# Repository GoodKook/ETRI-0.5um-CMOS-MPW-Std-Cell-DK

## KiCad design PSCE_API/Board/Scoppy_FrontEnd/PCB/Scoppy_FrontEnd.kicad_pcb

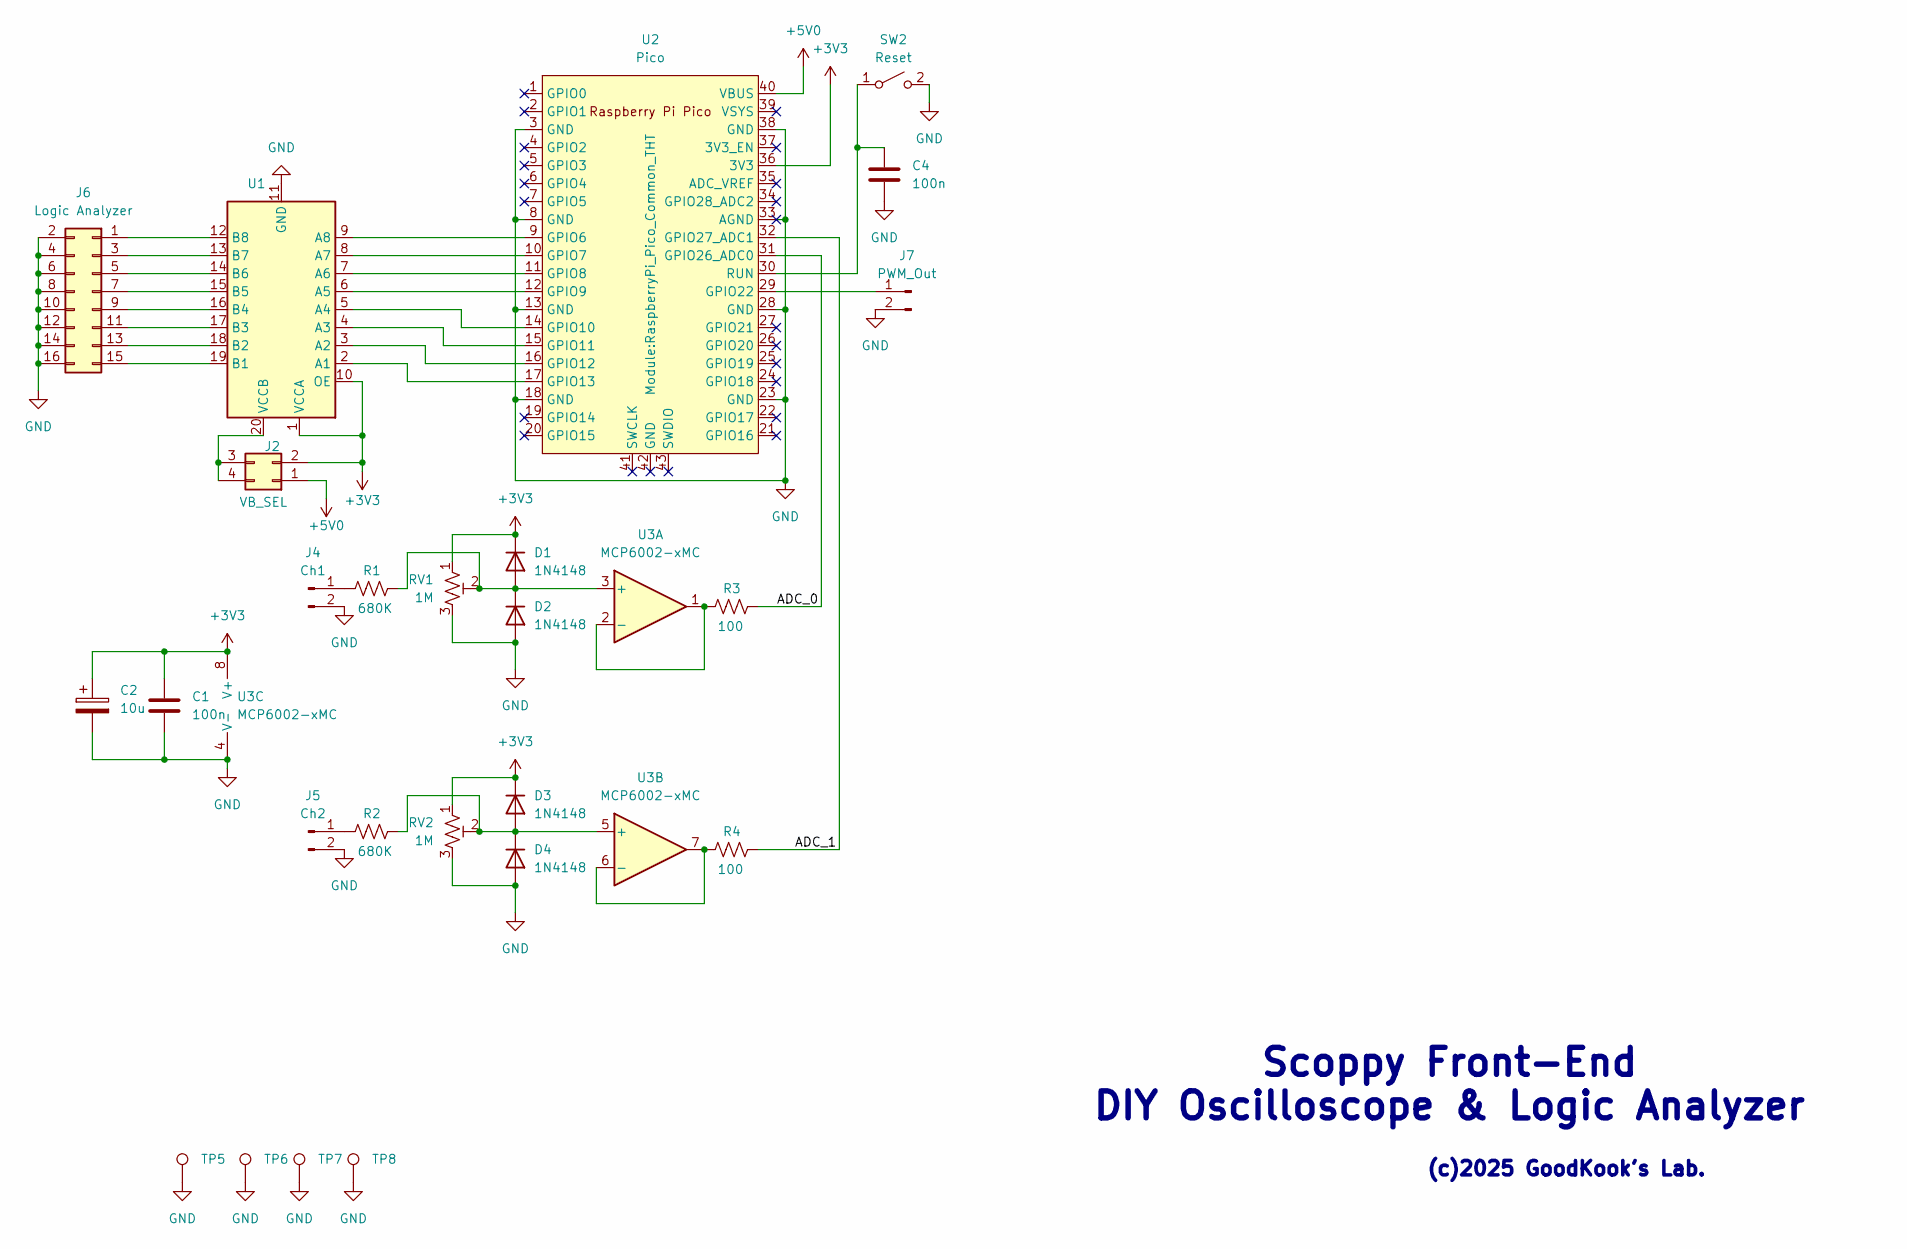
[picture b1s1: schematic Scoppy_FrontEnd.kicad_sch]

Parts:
C1, C4: 100n; C_Disc_D3.8mm_W2.6mm_P2.50mm
C2: 10u; CP_Radial_Tantal_D9.0mm_P2.50mm
D1, D2, D3, D4: 1N4148; D_DO-35_SOD27_P7.62mm_Horizontal
J2: VB_SEL; PinHeader_2x02_P2.54mm_Vertical
J4: Ch1; PinHeader_2x01_P2.54mm_Vertical
J5: Ch2; PinHeader_2x01_P2.54mm_Vertical
J6: Logic Analyzer; PinHeader_2x08_P2.54mm_Vertical
J7: PWM_Out; PinHeader_2x01_P2.54mm_Vertical
R1, R2: 680K; R_Axial_DIN0204_L3.6mm_D1.6mm_P7.62mm_Horizontal
R3, R4: 100; R_Axial_DIN0204_L3.6mm_D1.6mm_P7.62mm_Horizontal
RV1, RV2: 1M; Potentiometer_Runtron_RM-065_Vertical
SW2: Reset; SW_PUSH_6mm_H5mm
TP5, TP6, TP7, TP8: Mounting Hole; MountingHole_3.2mm_M3
U1: Level_Shifter_Module_HW-221
U2: Pico; RaspberryPi_Pico_Common_THT
U3: MCP6002-xMC; DIP-8_W10.16mm_LongPads

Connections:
+3V3: C1.1, C2.1, D1.1 (K), D3.1 (K), J2.2, RV1.1, RV2.1, U1.1 (VCCA), U1.10 (OE), U2.36 (3V3), U3.8 (V+)
+5V0: J2.1, U2.40 (VBUS)
/ADC_0: R3.1, U2.31 (GPIO26_ADC0)
/ADC_1: R4.1, U2.32 (GPIO27_ADC1)
GND: C1.2, C2.2, C4.2, D2.2 (A), D4.2 (A), J4.2, J5.2, J6.2, J6.4, J6.6, J6.8, J6.10, J6.12, J6.14, J6.16, J7.2, RV1.3, RV2.3, SW2.2 (B), TP5.1, TP6.1, TP7.1, TP8.1, U1.11 (GND), U2.3 (GND), U2.8 (GND), U2.13 (GND), U2.18 (GND), U2.23 (GND), U2.28 (GND), U2.33 (AGND), U2.38 (GND), U3.4 (V-), U3.9 (V-)
unnamed: D1.2 (A), D2.1 (K), R1.1, RV1.2, U3.3 (+)
unnamed: D3.2 (A), D4.1 (K), R2.1, RV2.2, U3.5 (+)
unnamed: J2.3, J2.4, U1.20 (VCCB)
unnamed: J4.1, R1.2
unnamed: J5.1, R2.2
unnamed: J6.1, U1.12 (B8)
unnamed: J6.3, U1.13 (B7)
unnamed: J6.5, U1.14 (B6)
unnamed: J6.7, U1.15 (B5)
unnamed: J6.9, U1.16 (B4)
unnamed: J6.11, U1.17 (B3)
unnamed: J6.13, U1.18 (B2)
unnamed: J6.15, U1.19 (B1)
unnamed: J7.1, U2.29 (GPIO22)
unnamed: C4.1, SW2.1 (A), U2.30 (RUN)
unnamed: U1.2 (A1), U2.17 (GPIO13)
unnamed: U1.3 (A2), U2.16 (GPIO12)
unnamed: U1.4 (A3), U2.15 (GPIO11)
unnamed: U1.5 (A4), U2.14 (GPIO10)
unnamed: U1.6 (A5), U2.12 (GPIO9)
unnamed: U1.7 (A6), U2.11 (GPIO8)
unnamed: U1.8 (A7), U2.10 (GPIO7)
unnamed: U1.9 (A8), U2.9 (GPIO6)
unnamed: R3.2, U3.1, U3.2 (-)
unnamed: R4.2, U3.6 (-), U3.7

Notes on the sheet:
Scoppy Front-End DIY Oscilloscope & Logic Analyzer
(c)2025 GoodKook's Lab.

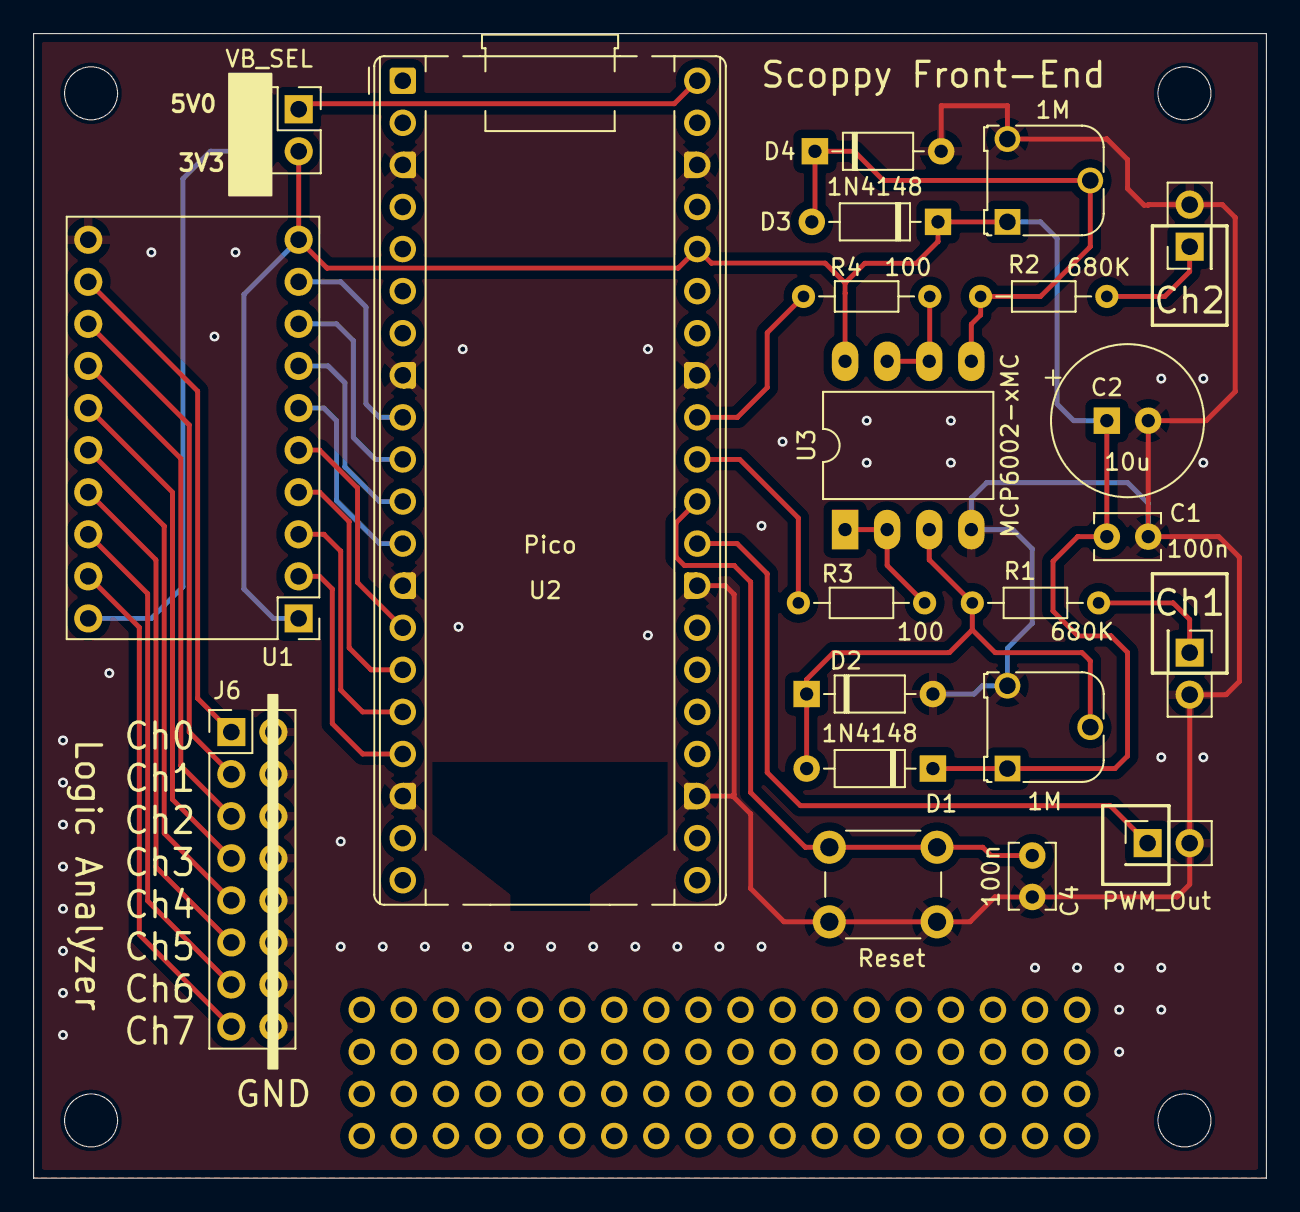
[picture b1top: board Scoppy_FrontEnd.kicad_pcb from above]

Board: 2 copper layers, 74.4 x 69.1 mm, 26 parts (0 on the bottom side), 30 nets.

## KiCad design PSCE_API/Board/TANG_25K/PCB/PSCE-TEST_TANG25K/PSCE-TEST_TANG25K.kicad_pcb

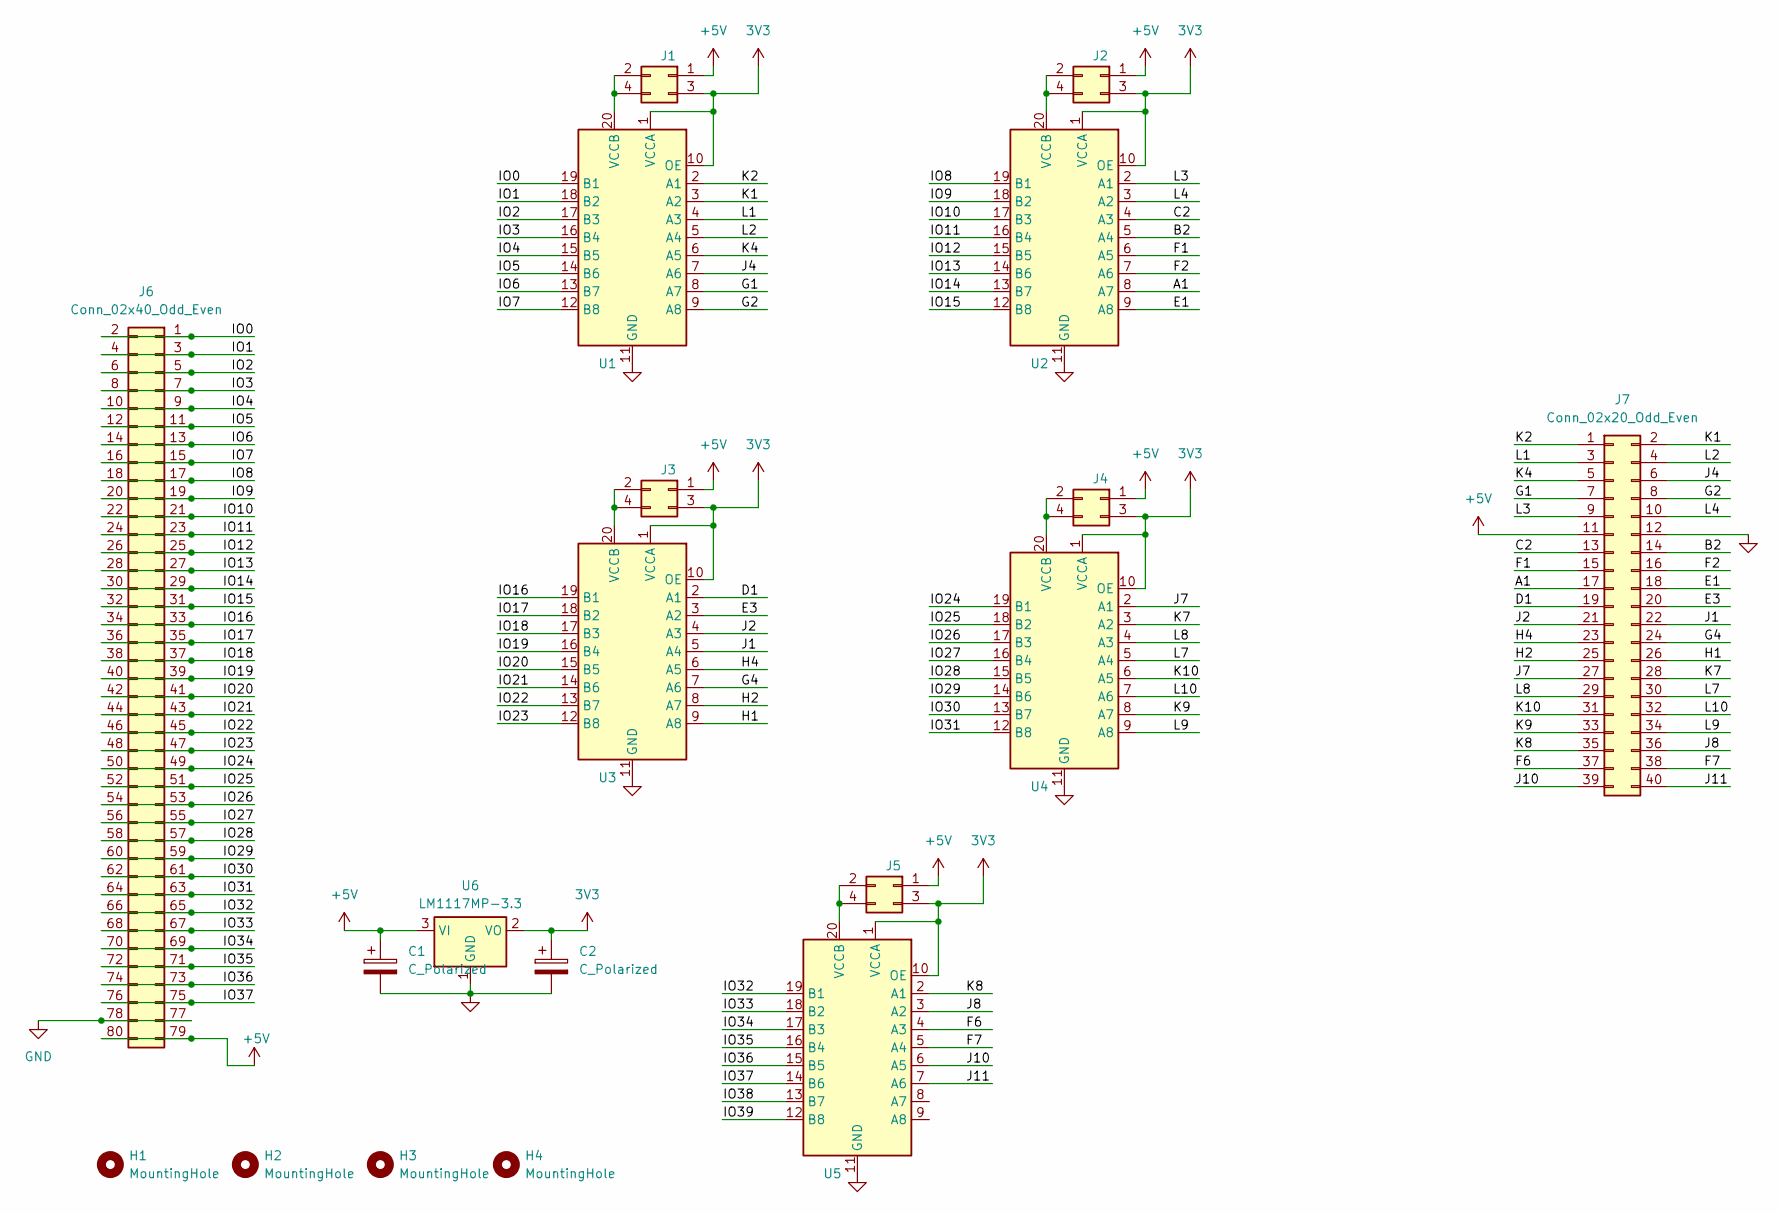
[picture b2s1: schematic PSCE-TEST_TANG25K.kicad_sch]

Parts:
C1, C2: C_Polarized; C_1206_3216Metric_Pad1.33x1.80mm_HandSolder
H1, H2, H3, H4: MountingHole; MountingHole_3.5mm
J1, J2, J3, J4, J5: Conn_02x02_Odd_Even; PinHeader_2x02_P2.54mm_Vertical
J6: Conn_02x40_Odd_Even; PinHeader_2x40_P2.54mm_Vertical
J7: Conn_02x20_Odd_Even; PinHeader_2x20_P2.54mm_Vertical
U1, U2, U3, U4, U5: Level_Shifter_Module_HW-221
U6: LM1117MP-3.3; SOT-223-3_TabPin2

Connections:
3V3: C2.1, J1.3, J2.3, J3.3, J4.3, J5.3, U1.1 (VCCA), U1.10 (OE), U2.1 (VCCA), U2.10 (OE), U3.1 (VCCA), U3.10 (OE), U4.1 (VCCA), U4.10 (OE), U5.1 (VCCA), U5.10 (OE), U6.2 (VO)
+5V: C1.1, J1.1, J2.1, J3.1, J4.1, J5.1, J6.79, J6.80, J7.11, U6.3 (VI)
/A1: J7.17, U2.8 (A7)
/B2: J7.14, U2.5 (A4)
/C2: J7.13, U2.4 (A3)
/D1: J7.19, U3.2 (A1)
/E1: J7.18, U2.9 (A8)
/E3: J7.20, U3.3 (A2)
/F1: J7.15, U2.6 (A5)
/F2: J7.16, U2.7 (A6)
/F6: J7.37, U5.4 (A3)
/F7: J7.38, U5.5 (A4)
/G1: J7.7, U1.8 (A7)
/G2: J7.8, U1.9 (A8)
/G4: J7.24, U3.7 (A6)
/H1: J7.26, U3.9 (A8)
/H2: J7.25, U3.8 (A7)
/H4: J7.23, U3.6 (A5)
/IO0: J6.1, J6.2, U1.19 (B1)
/IO1: J6.3, J6.4, U1.18 (B2)
/IO2: J6.5, J6.6, U1.17 (B3)
/IO3: J6.7, J6.8, U1.16 (B4)
/IO4: J6.9, J6.10, U1.15 (B5)
/IO5: J6.11, J6.12, U1.14 (B6)
/IO6: J6.13, J6.14, U1.13 (B7)
/IO7: J6.15, J6.16, U1.12 (B8)
/IO8: J6.17, J6.18, U2.19 (B1)
/IO9: J6.19, J6.20, U2.18 (B2)
/IO10: J6.21, J6.22, U2.17 (B3)
/IO11: J6.23, J6.24, U2.16 (B4)
/IO12: J6.25, J6.26, U2.15 (B5)
/IO13: J6.27, J6.28, U2.14 (B6)
/IO14: J6.29, J6.30, U2.13 (B7)
/IO15: J6.31, J6.32, U2.12 (B8)
/IO16: J6.33, J6.34, U3.19 (B1)
/IO17: J6.35, J6.36, U3.18 (B2)
/IO18: J6.37, J6.38, U3.17 (B3)
/IO19: J6.39, J6.40, U3.16 (B4)
/IO20: J6.41, J6.42, U3.15 (B5)
/IO21: J6.43, J6.44, U3.14 (B6)
/IO22: J6.45, J6.46, U3.13 (B7)
/IO23: J6.47, J6.48, U3.12 (B8)
/IO24: J6.49, J6.50, U4.19 (B1)
/IO25: J6.51, J6.52, U4.18 (B2)
/IO26: J6.53, J6.54, U4.17 (B3)
/IO27: J6.55, J6.56, U4.16 (B4)
/IO28: J6.57, J6.58, U4.15 (B5)
/IO29: J6.59, J6.60, U4.14 (B6)
/IO30: J6.61, J6.62, U4.13 (B7)
/IO31: J6.63, J6.64, U4.12 (B8)
/IO32: J6.65, J6.66, U5.19 (B1)
/IO33: J6.67, J6.68, U5.18 (B2)
/IO34: J6.69, J6.70, U5.17 (B3)
/IO35: J6.71, J6.72, U5.16 (B4)
/IO36: J6.73, J6.74, U5.15 (B5)
/IO37: J6.75, J6.76, U5.14 (B6)
/IO38: U5.13 (B7)
/IO39: U5.12 (B8)
/J1: J7.22, U3.5 (A4)
/J2: J7.21, U3.4 (A3)
/J4: J7.6, U1.7 (A6)
/J7: J7.27, U4.2 (A1)
/J8: J7.36, U5.3 (A2)
/J10: J7.39, U5.6 (A5)
/J11: J7.40, U5.7 (A6)
/K1: J7.2, U1.3 (A2)
/K2: J7.1, U1.2 (A1)
/K4: J7.5, U1.6 (A5)
/K7: J7.28, U4.3 (A2)
/K8: J7.35, U5.2 (A1)
/K9: J7.33, U4.8 (A7)
/K10: J7.31, U4.6 (A5)
/L1: J7.3, U1.4 (A3)
/L2: J7.4, U1.5 (A4)
/L3: J7.9, U2.2 (A1)
/L4: J7.10, U2.3 (A2)
/L7: J7.30, U4.5 (A4)
/L8: J7.29, U4.4 (A3)
/L9: J7.34, U4.9 (A8)
/L10: J7.32, U4.7 (A6)
GND: C1.2, C2.2, J6.77, J6.78, J7.12, U1.11 (GND), U2.11 (GND), U3.11 (GND), U4.11 (GND), U5.11 (GND), U6.1 (GND)
unnamed: J1.2, J1.4, U1.20 (VCCB)
unnamed: J2.2, J2.4, U2.20 (VCCB)
unnamed: J3.2, J3.4, U3.20 (VCCB)
unnamed: J4.2, J4.4, U4.20 (VCCB)
unnamed: J5.2, J5.4, U5.20 (VCCB)

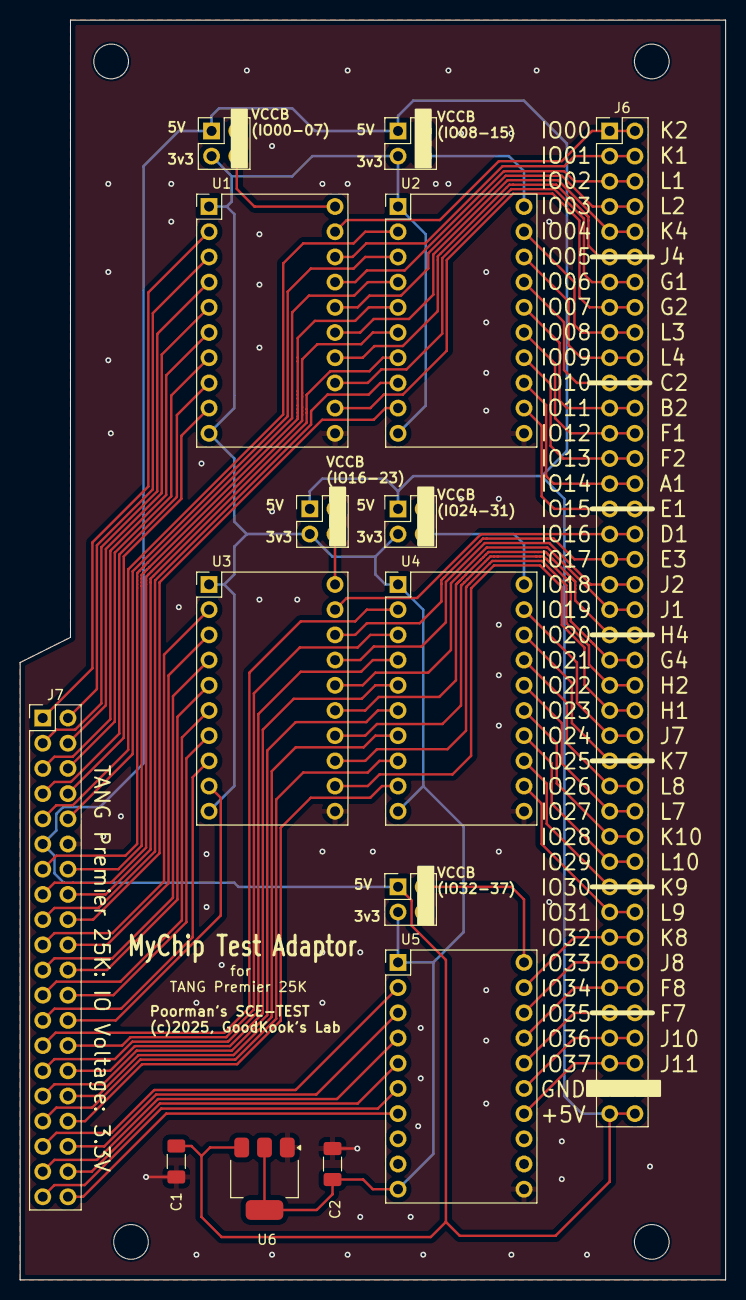
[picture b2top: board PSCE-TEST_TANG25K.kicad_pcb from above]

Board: 2 copper layers, 71.1 x 127.0 mm, 19 parts (0 on the bottom side), 84 nets.

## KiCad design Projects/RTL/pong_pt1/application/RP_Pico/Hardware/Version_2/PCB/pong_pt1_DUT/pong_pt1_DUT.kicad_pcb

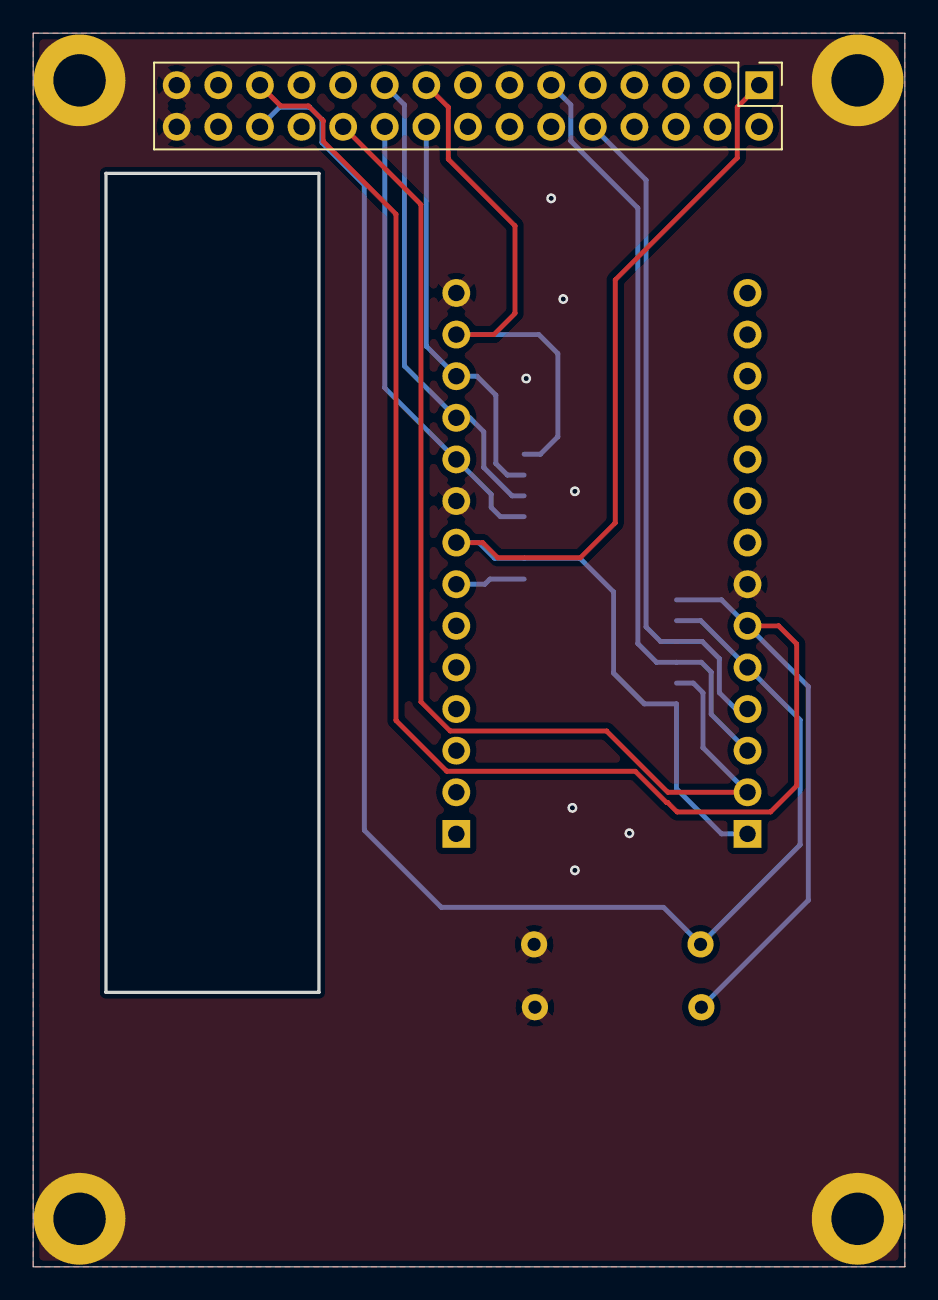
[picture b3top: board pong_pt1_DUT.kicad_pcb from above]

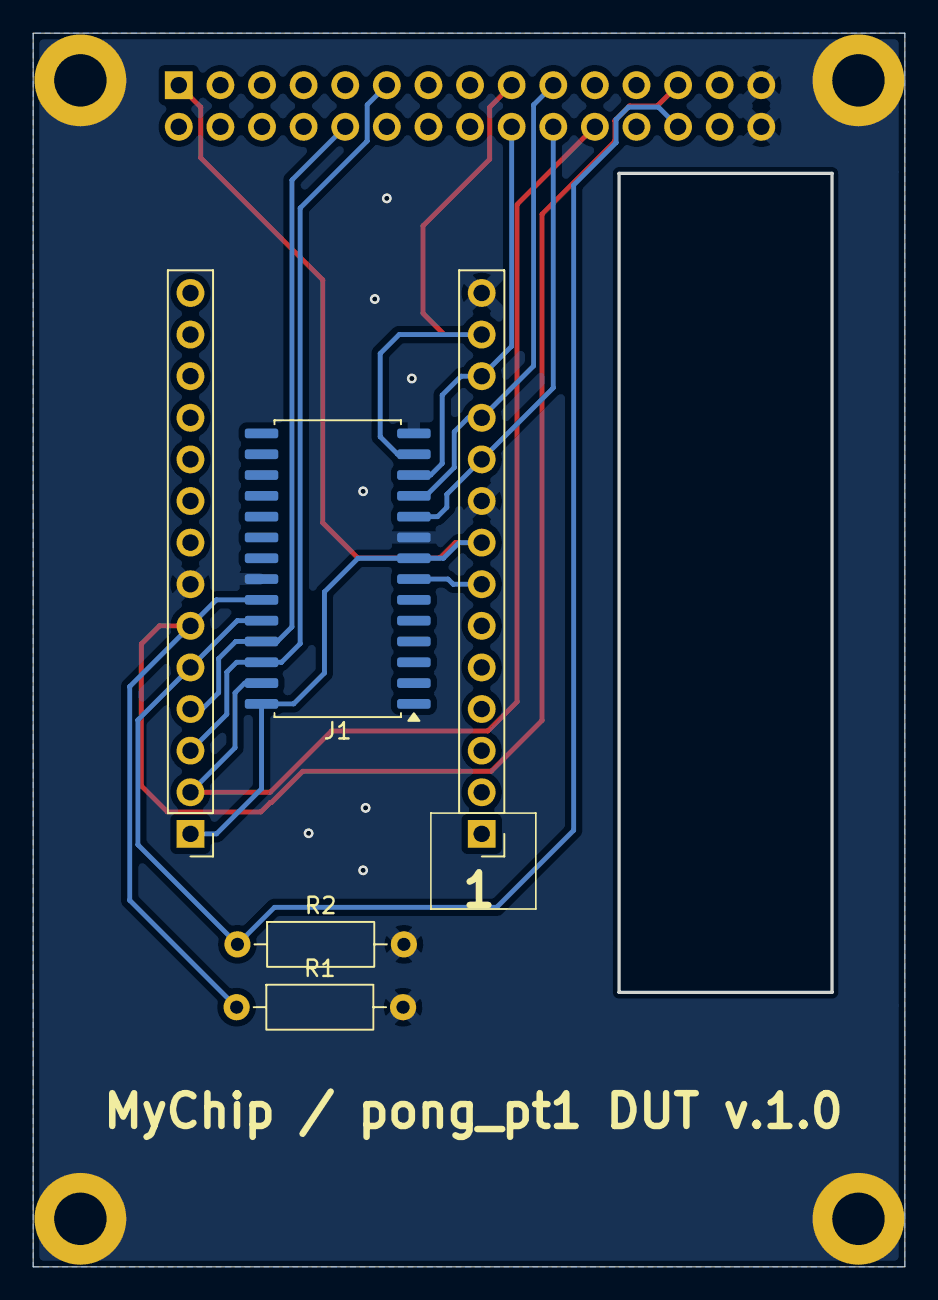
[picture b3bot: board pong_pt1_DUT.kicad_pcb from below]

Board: 2 copper layers, 53.2 x 75.3 mm, 10 parts (5 on the bottom side), 12 nets.

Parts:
H1, H2, H5, H6: MountingHole_Pad; MountingHole_3.2mm_M3_DIN965_Pad
J1: MyChip; SOIC-28W_7.5x17.9mm_P1.27mm
J2: MyChip_L; PinHeader_1x14_P2.54mm_Vertical
J3: MyChip_R; PinHeader_1x14_P2.54mm_Vertical
J4: Conn_02x15_Odd_Even; PinHeader_2x15_P2.54mm_Vertical
R1, R2: 47K; R_Axial_DIN0207_L6.3mm_D2.5mm_P10.16mm_Horizontal

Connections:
+3V3: J1.8, J1.28, J2.8, J3.1, J4.1
/clk: J1.27, J3.2, J4.22
/down: J1.24, J3.5, J4.26, R2.1
/enable: J1.26, J3.3, J4.11
/hsync: J1.12, J2.12, J4.18
/p_tick: J1.13, J2.13, J4.17
/reset: J1.25, J3.4, J4.10
/rgb: J1.10, J2.10, J4.20
/up: J1.23, J3.6, J4.25, R1.1
/vsync: J1.11, J2.11, J4.19
GND: H1.1 (1_1), H2.1 (1_1), H5.1 (1_1), H6.1 (1_1), J1.9, J1.14, J1.22, J2.9, J2.14, J3.7, J4.29, J4.30, R1.2, R2.2
unnamed: J1.7, J2.7

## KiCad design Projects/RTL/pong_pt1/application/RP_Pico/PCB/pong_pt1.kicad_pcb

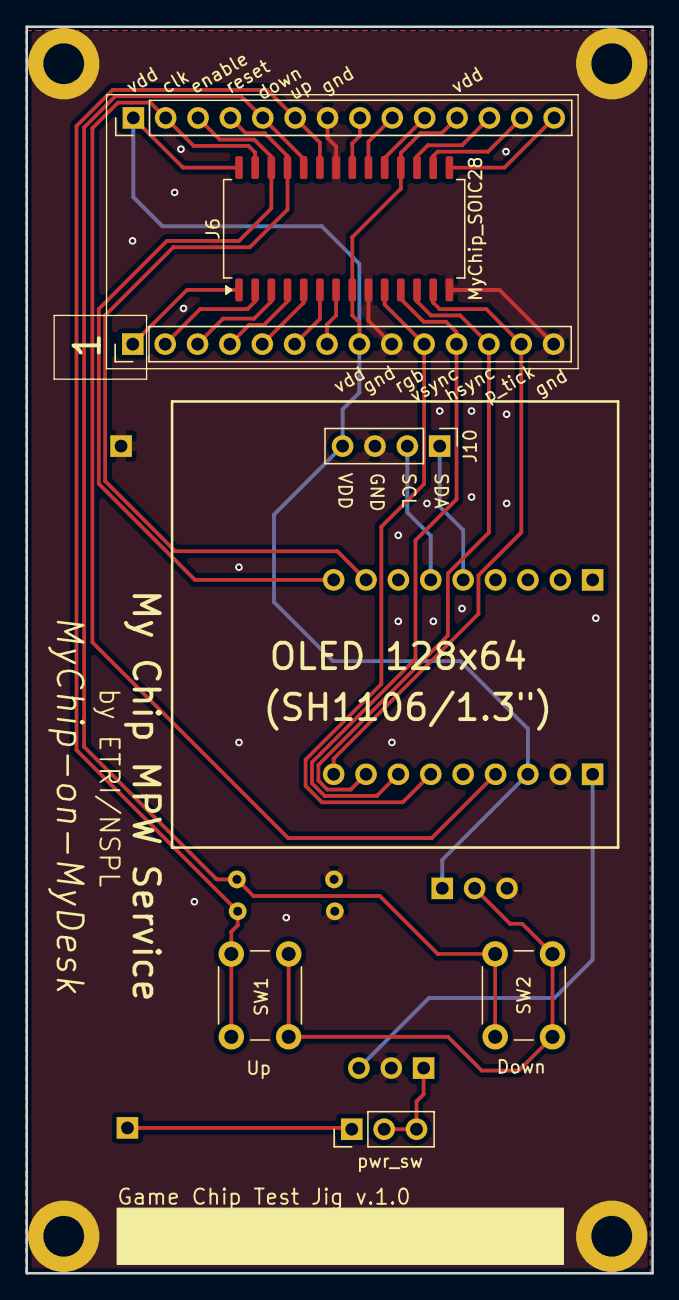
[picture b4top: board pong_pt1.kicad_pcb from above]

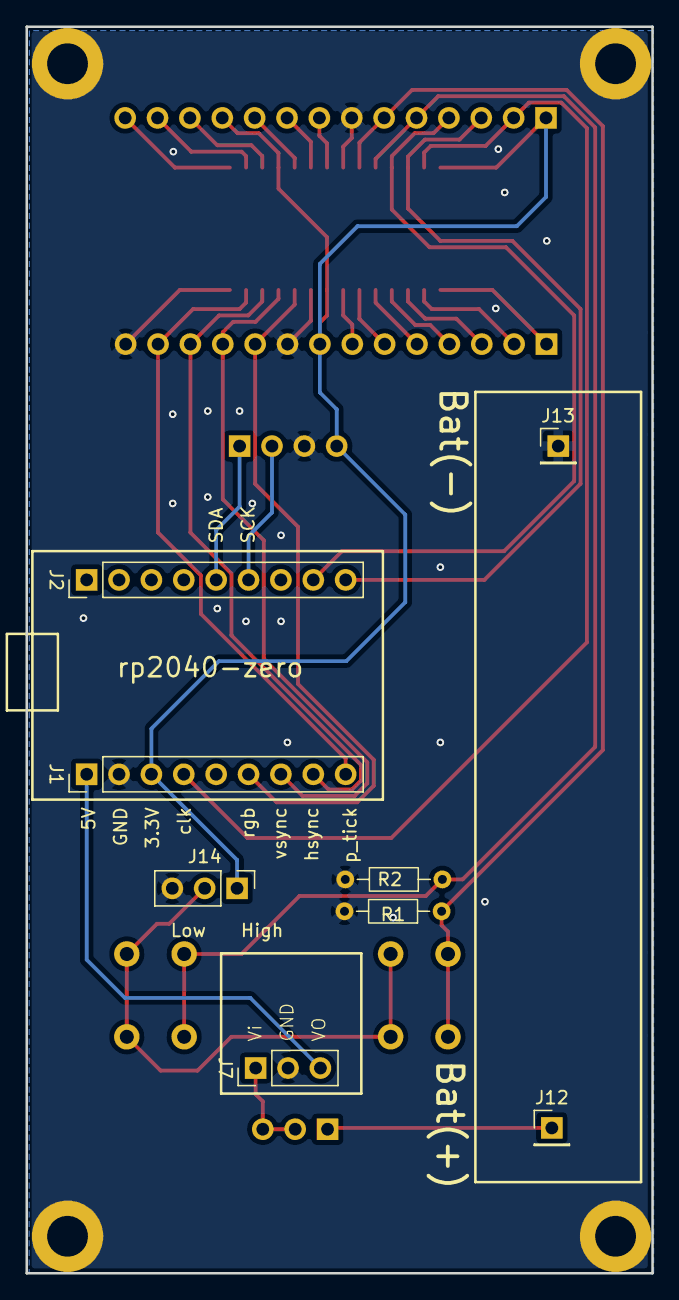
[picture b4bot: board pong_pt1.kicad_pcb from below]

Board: 2 copper layers, 49.1 x 97.8 mm, 19 parts (8 on the bottom side), 24 nets.

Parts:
H1, H2, H5, H6: MountingHole_Pad; MountingHole_3.2mm_M3_DIN965_Pad
J1: RP_L; PinHeader_1x09_P2.54mm_Vertical
J2: RP_R; PinHeader_1x09_P2.54mm_Vertical
J4: L; PinHeader_1x14_P2.54mm_Vertical
J5: R; PinHeader_1x14_P2.54mm_Vertical
J6: MyChip_SOIC28; SOIC-28W_7.5x18.7mm_P1.27mm
J7: DC-DC; PinHeader_1x03_P2.54mm_Vertical
J10: OLED128x64; PinHeader_1x04_P2.54mm_Vertical
J11: pwr_sw; PinHeader_1x03_P2.54mm_Vertical
J12: Bat(+); PinHeader_1x01_P2.54mm_Vertical
J13: Bat(-); PinHeader_1x01_P2.54mm_Vertical
J14: PinHeader_1x03_P2.54mm_Vertical
R1, R2: 47K; R_Axial_DIN0204_L3.6mm_D1.6mm_P7.62mm_Horizontal
SW1: Up; SW_PUSH_6mm
SW2: Down; SW_PUSH_6mm

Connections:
+3V3: J1.3, J4.8, J5.1, J5.11, J6.8, J6.18, J6.28, J10.4, J14.1
+5V: J1.1, J7.3
/Bat+: J11.1, J12.1 (Pin_1_1)
/COMM: J14.2, SW1.2, SW2.2
/SCL: J2.6, J10.2
/SDA: J2.5, J10.1
/Vi: J7.1, J11.2, J11.3
/clk: J1.4, J5.2, J6.27
/down: J5.5, J6.24, R2.1, SW2.1
/enable: J2.9, J5.3, J6.26
/hsync: J1.8, J4.12, J6.12
/p_tick: J1.9, J4.13, J6.13
/reset: J2.8, J5.4, J6.25
/rgb: J1.6, J4.10, J6.10
/up: J5.6, J6.23, R1.1, SW1.1
/vsync: J1.7, J4.11, J6.11
GND: H1.1 (1_1), H2.1 (1_1), H5.1 (1_1), H6.1 (1_1), J1.2, J4.9, J4.14, J5.7, J6.9, J6.14, J6.22, J7.2, J10.3, J13.1 (Pin_1_1), J14.3, R1.2, R2.2
unnamed: J4.1, J6.1
unnamed: J4.2, J6.2
unnamed: J4.3, J6.3
unnamed: J4.4, J6.4
unnamed: J4.5, J6.5
unnamed: J4.6, J6.6
unnamed: J4.7, J6.7

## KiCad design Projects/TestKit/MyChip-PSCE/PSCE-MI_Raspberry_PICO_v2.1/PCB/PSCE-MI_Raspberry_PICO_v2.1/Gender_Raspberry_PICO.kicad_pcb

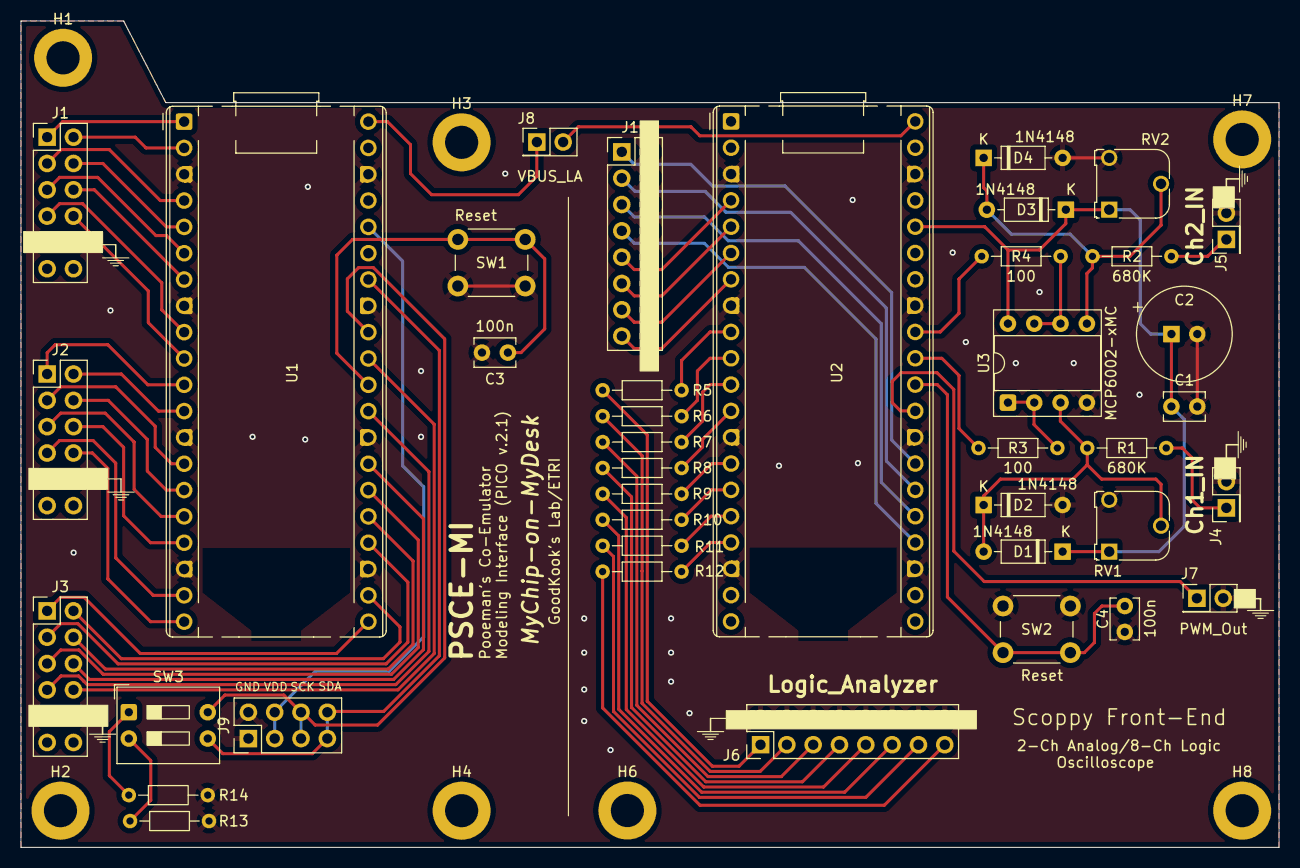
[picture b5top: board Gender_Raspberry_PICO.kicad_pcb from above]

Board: 2 copper layers, 121.4 x 79.8 mm, 47 parts (0 on the bottom side), 68 nets.

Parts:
C1, C3, C4: 100n; C_Disc_D3.8mm_W2.6mm_P2.50mm
C2: 10u; CP_Radial_Tantal_D9.0mm_P2.50mm
D1, D2, D3, D4: 1N4148; D_DO-35_SOD27_P7.62mm_Horizontal
H1, H2, H3, H4, H6, H7, H8: MountingHole; MountingHole_3.2mm_M3_DIN965_Pad
J1: FPGA_A; PinHeader_2x06_P2.54mm_Vertical
J2: FPGA_B; PinHeader_2x06_P2.54mm_Vertical
J3: FPGA_C; PinHeader_2x06_P2.54mm_Vertical
J4: Ch1_IN; PinHeader_2x01_P2.54mm_Vertical
J5: Ch2_IN; PinHeader_2x01_P2.54mm_Vertical
J6: Logic_Analyzer; PinHeader_2x08_P2.54mm_Vertical
J7: PWM_Out; PinHeader_2x01_P2.54mm_Vertical
J8: VBUS_LA; PinHeader_2x01_P2.54mm_Vertical
J9: Soft_I2C; PinHeader_2x04_P2.54mm_Vertical
J10: AUX; PinHeader_2x08_P2.54mm_Vertical
R1, R2: 680K; R_Axial_DIN0204_L3.6mm_D1.6mm_P7.62mm_Horizontal
R3, R4, R5, R6, R7, R8, R9, R10, R11, R12: 100; R_Axial_DIN0204_L3.6mm_D1.6mm_P7.62mm_Horizontal
R13, R14: 4.7K; R_Axial_DIN0204_L3.6mm_D1.6mm_P7.62mm_Horizontal
RV1, RV2: 1M; Potentiometer_Runtron_RM-065_Vertical
SW1, SW2: Reset; SW_PUSH_6mm_H9.5mm
SW3: SW_DIP_x02; SW_DIP_SPSTx02_Slide_9.78x7.26mm_W7.62mm_P2.54mm
U1, U2: Pico; RaspberryPi_Pico_Common_THT
U3: MCP6002-xMC; DIP-8_W7.62mm_Socket

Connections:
+3V3: C1.1, C2.1, D1.1 (K), D3.1 (K), RV1.1, RV2.1, U2.36 (3V3), U3.8 (V+)
+5V: J8.1, U1.40 (VBUS)
/ADC_0: R3.1, U2.31 (GPIO26_ADC0)
/ADC_1: R4.1, U2.32 (GPIO27_ADC1)
/AUX_2: J10.9, U2.4 (GPIO2)
/AUX_3: J10.11, U2.5 (GPIO3)
/AUX_4: J10.13, U2.6 (GPIO4)
/AUX_5: J10.15, U2.7 (GPIO5)
/AUX_18: J10.7, U2.24 (GPIO18)
/AUX_19: J10.5, U2.25 (GPIO19)
/AUX_20: J10.3, U2.26 (GPIO20)
/AUX_21: J10.1, U2.27 (GPIO21)
/FPGA_0: J1.1, U1.1 (GPIO0)
/FPGA_1: J1.2, U1.2 (GPIO1)
/FPGA_2: J1.3, U1.4 (GPIO2)
/FPGA_3: J1.4, U1.5 (GPIO3)
/FPGA_4: J1.5, U1.6 (GPIO4)
/FPGA_5: J1.6, U1.7 (GPIO5)
/FPGA_6: J1.7, U1.9 (GPIO6)
/FPGA_7: J1.8, U1.10 (GPIO7)
/FPGA_8: J2.1, U1.11 (GPIO8)
/FPGA_9: J2.2, U1.12 (GPIO9)
/FPGA_10: J2.3, U1.14 (GPIO10)
/FPGA_11: J2.4, U1.15 (GPIO11)
/FPGA_12: J2.5, U1.16 (GPIO12)
/FPGA_13: J2.6, U1.17 (GPIO13)
/FPGA_14: J2.7, U1.19 (GPIO14)
/FPGA_15: J2.8, U1.20 (GPIO15)
/FPGA_16: J3.1, U1.21 (GPIO16)
/FPGA_17: J3.2, U1.22 (GPIO17)
/FPGA_18: J3.3, U1.24 (GPIO18)
/FPGA_19: J3.4, U1.25 (GPIO19)
/FPGA_20: J3.5, U1.26 (GPIO20)
/FPGA_21: J3.6, U1.27 (GPIO21)
/FPGA_22: J3.7, U1.29 (GPIO22)
/FPGA_23: J3.8, U1.31 (GPIO26_ADC0)
/SCK: J9.5, J9.6, SW3.4, U1.32 (GPIO27_ADC1)
/SDA: J9.7, J9.8, SW3.3, U1.34 (GPIO28_ADC2)
GND: C1.2, C2.2, C3.2, C4.2, D2.2 (A), D4.2 (A), J1.9, J1.10, J2.9, J2.10, J3.9, J3.10, J4.2, J5.2, J6.2, J6.4, J6.6, J6.8, J6.10, J6.12, J6.14, J6.16, J7.2, J9.1, J9.2, J10.2, J10.4, J10.6, J10.8, J10.10, J10.12, J10.14, J10.16, R13.2, R14.2, RV1.3, RV2.3, SW1.3 (K), SW1.4 (A), SW2.3 (K), SW2.4 (A), U1.3 (GND), U1.8 (GND), U1.13 (GND), U1.18 (GND), U1.23 (GND), U1.28 (GND), U1.33 (AGND), U1.38 (GND), U2.3 (GND), U2.8 (GND), U2.13 (GND), U2.18 (GND), U2.23 (GND), U2.28 (GND), U2.33 (AGND), U2.38 (GND), U3.4 (V-)
unnamed: D1.2 (A), D2.1 (K), R1.1, RV1.2, U3.3 (+)
unnamed: D3.2 (A), D4.1 (K), R2.1, RV2.2, U3.5 (+)
unnamed: J4.1, R1.2
unnamed: J5.1, R2.2
unnamed: J6.1, R5.1
unnamed: J6.3, R6.1
unnamed: J6.5, R7.1
unnamed: J6.7, R8.1
unnamed: J6.9, R9.1
unnamed: J6.11, R10.1
unnamed: J6.13, R11.1
unnamed: J6.15, R12.1
unnamed: J7.1, U2.29 (GPIO22)
unnamed: J8.2, U2.40 (VBUS)
unnamed: J9.3, J9.4, U1.36 (3V3)
unnamed: R13.1, SW3.2
unnamed: R14.1, SW3.1
unnamed: C3.1, SW1.1, SW1.2, U1.30 (RUN)
unnamed: R5.2, U2.9 (GPIO6)
unnamed: R6.2, U2.10 (GPIO7)
unnamed: R7.2, U2.11 (GPIO8)
unnamed: R8.2, U2.12 (GPIO9)
unnamed: R9.2, U2.14 (GPIO10)
unnamed: R10.2, U2.15 (GPIO11)
unnamed: R11.2, U2.16 (GPIO12)
unnamed: R12.2, U2.17 (GPIO13)
unnamed: C4.1, SW2.1, SW2.2, U2.30 (RUN)
unnamed: R3.2, U3.1, U3.2 (-)
unnamed: R4.2, U3.6 (-), U3.7
